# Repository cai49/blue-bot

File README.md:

# Blue Bot Cartesian Robot
Work in progress...

## Python Requirements
Create a new environment
```python -m venv /path/to/new/virtual/environment```

Install all 
```pip install -r requirements.txt```

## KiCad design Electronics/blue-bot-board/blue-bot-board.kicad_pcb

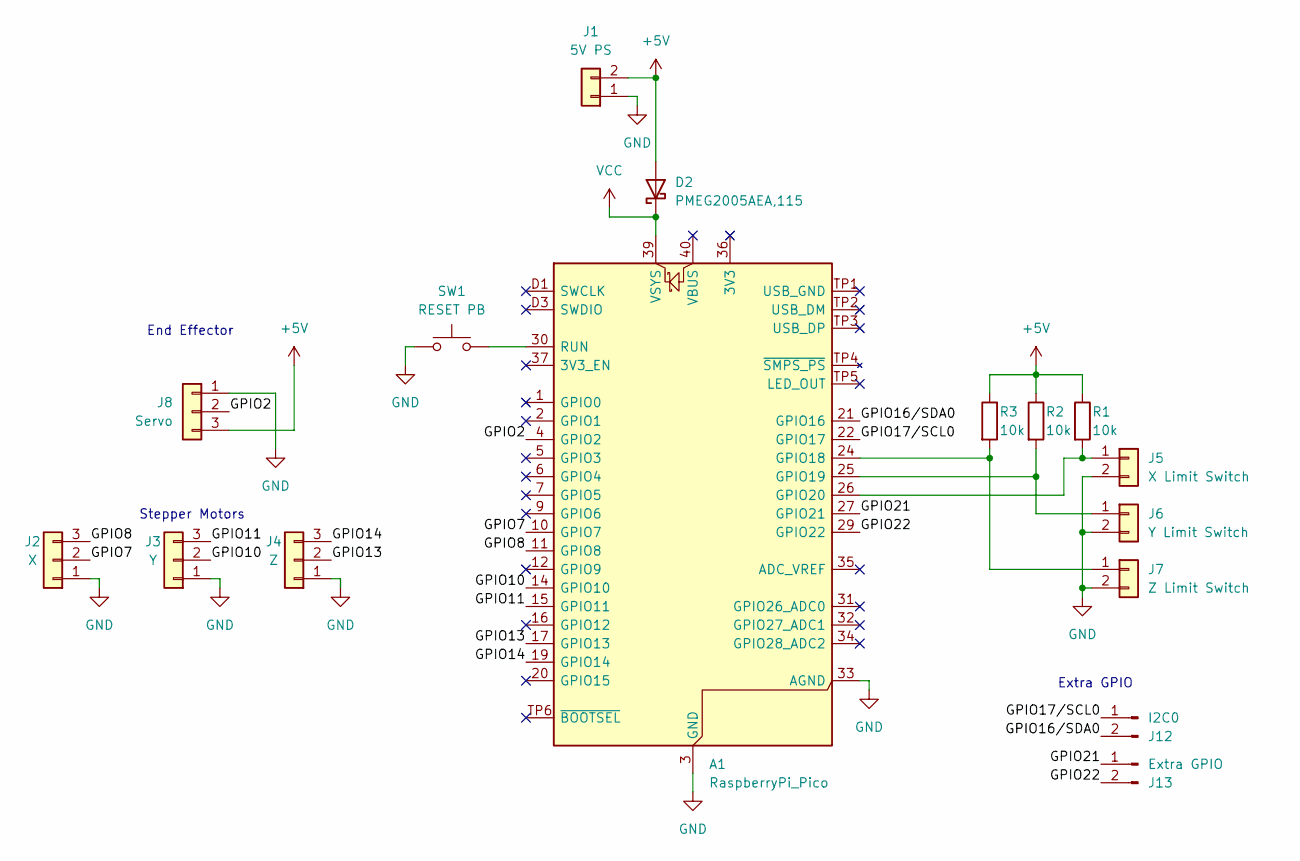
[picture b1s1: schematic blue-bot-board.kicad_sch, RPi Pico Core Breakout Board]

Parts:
A1: RaspberryPi_Pico; RaspberryPi_Pico_SMD
D2: PMEG2005AEA,115; D_A-405_P7.62mm_Horizontal; LCSC C179428
J1: 5V PS; TerminalBlock_Phoenix_MKDS-1,5-2-5.08_1x02_P5.08mm_Horizont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
J2: X; TerminalBlock_Phoenix_MKDS-1,5-3-5.08_1x03_P5.08mm_Horizont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
J3: Y; TerminalBlock_Phoenix_MKDS-1,5-3-5.08_1x03_P5.08mm_Horizont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
J4: Z; TerminalBlock_Phoenix_MKDS-1,5-3-5.08_1x03_P5.08mm_Horizont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
J5: X Limit Switch; JST_PH_B2B-PH-K_1x02_P2.00mm_Vertical
J6: Y Limit Switch; JST_PH_B2B-PH-K_1x02_P2.00mm_Vertical
J7: Z Limit Switch; JST_PH_B2B-PH-K_1x02_P2.00mm_Vertical
J8: Servo; JST_PH_B3B-PH-K_1x03_P2.00mm_Vertical
J12: I2C0; PinHeader_1x02_P2.54mm_Vertical
J13: Extra GPIO; PinHeader_1x02_P2.54mm_Vertical
R1, R2, R3: 10k; R_Axial_DIN0207_L6.3mm_D2.5mm_P10.16mm_Horizontal; LCSC C4013692
SW1: RESET PB; SW_PUSH_6mm

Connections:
+5V: D2.2 (A), J1.2, J8.3, R1.1, R2.1, R3.1
/GPIO2: A1.4 (GPIO2), J8.2
/GPIO7: A1.10 (GPIO7), J2.2
/GPIO8: A1.11 (GPIO8), J2.3
/GPIO10: A1.14 (GPIO10), J3.2
/GPIO11: A1.15 (GPIO11), J3.3
/GPIO13: A1.17 (GPIO13), J4.2
/GPIO14: A1.19 (GPIO14), J4.3
/GPIO16/SDA0: A1.21 (GPIO16), J12.2
/GPIO17/SCL0: A1.22 (GPIO17), J12.1
/GPIO21: A1.27 (GPIO21), J13.1
/GPIO22: A1.29 (GPIO22), J13.2
GND: A1.3 (GND), A1.8 (GND), A1.13 (GND), A1.18 (GND), A1.23 (GND), A1.28 (GND), A1.33 (AGND), A1.38 (GND), A1.D2 (GND), J1.1, J2.1, J3.1, J4.1, J5.2, J6.2, J7.2, J8.1, SW1.1
unnamed: A1.24 (GPIO18), J7.1, R3.2
unnamed: A1.25 (GPIO19), J6.1, R2.2
unnamed: A1.26 (GPIO20), J5.1, R1.2
unnamed: A1.30 (RUN), SW1.2
VCC: A1.39 (VSYS), D2.1 (K)

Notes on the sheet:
End Effector
Stepper Motors
Extra GPIO

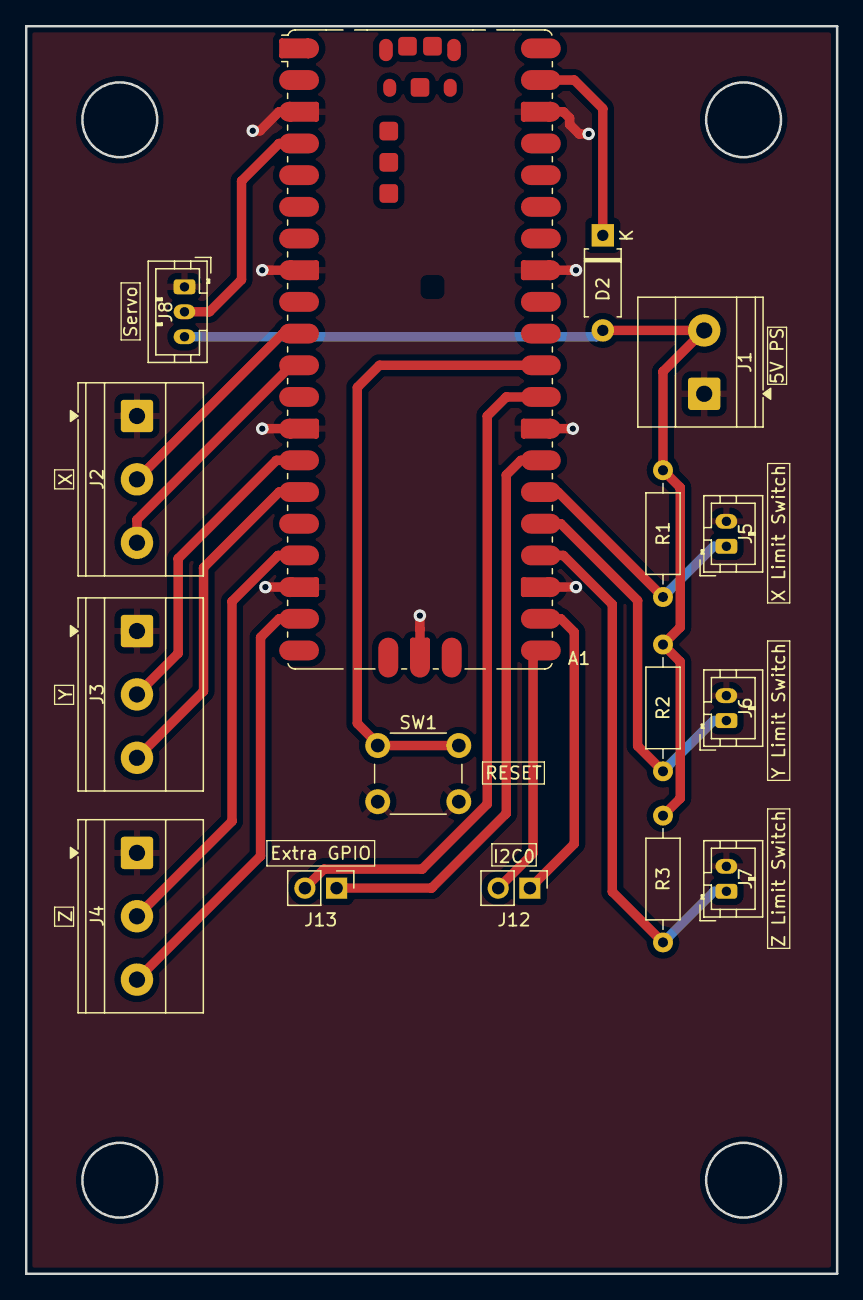
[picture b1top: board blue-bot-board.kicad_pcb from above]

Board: 2 copper layers, 65.0 x 100.0 mm, 16 parts (0 on the bottom side), 18 nets.

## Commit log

2025-04-07 Create Both Arduino and Python Slave Program
2025-04-07 Create Python Environment and Setup Script
2025-04-07 Continue the TODO file
2025-04-13 Implement CLI Arguments
2025-04-16 Add Labview Test
2025-04-19 Can use a RPico board with special flag
2025-04-19 Can use a RPico board with special flag
    Can use a RPico board with special flag
    Can use a RPico board with special flag
2025-04-20 Add MicroPython Demo for dual-core i2c interfacing with OLED screen
2025-04-23 add mockup interface
2025-04-24 Update Automated Install Script
2025-04-27 Add Servo todo file
2025-05-01 Create Test for multiple steppers using Arduino
2025-05-01 Update FrameController demo and diagram
2025-05-04 Test Stepper ping pong demo Create calculations sheet for step to mm translation Create subroutine headers for zero position sensing using Stepper motors and Limit switches
2025-05-11 Develop Zeroing Routines
2025-05-13 Create Schematics and PCB
2025-05-13 Update PCB to production
2025-05-19 Update Codebase for first test
    - Updating code while being connected (voltage OR) [ok]
    - Make servo work under given range [ok]
    - Create Stepper test [pending]
2025-05-24 PCB Test Successful
2025-05-31 Firmware RC-1
2025-06-01 Firmware v1.0
